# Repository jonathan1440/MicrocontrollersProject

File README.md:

# MicrocontrollersProject
 Hands-free deodorant dispenser

## Parts List
- 3x 1µF capacitors
- 1x 10µF capacitor
- 1x 2x3 header
- 1x 1x3 header
- 1x 1x4 header
- 1x transistor
- 1x Q3 crystal
- 2x 22 Ohm resistors
- 3x 10k Ohm resistors
- 2x buttons
- 1x 3 prong switch
- 1x AT90USB162 chip
- 1x USB micro B port
- 1x servo
- 1x Sharp GP2D02 IR sensor

## User Instructions
Flip the switch to on. Position yourself directly in front of the sensor. To tirgger the servo, move within 8-13 cm of the sensor. To release the servo, don't be within 8-13cm of the sensor.

## Code Overview
Pinout:
- PC7 - "on/off" switch
- PB5 - sensor output
- PB6 - sensor Vin
- PB7 - servo

GetDist() reads the data value from the IR sensor. The biggest roadblock was figguring out that the IR sensor was open drain. Otherwise the function just follows the Sharp GP2302 datasheet.

The main() function configures the pinout and initializes the PWM timer (clear OC0A at match, fast PWM mode, top defaults to 0xFF, prescaler = 64). The while loop waits until the switch is positioned at "on," and then moves the servo to the appropriate position if the user is within range or out of range. If the user is not detected by the sensor, the servo is turned off.

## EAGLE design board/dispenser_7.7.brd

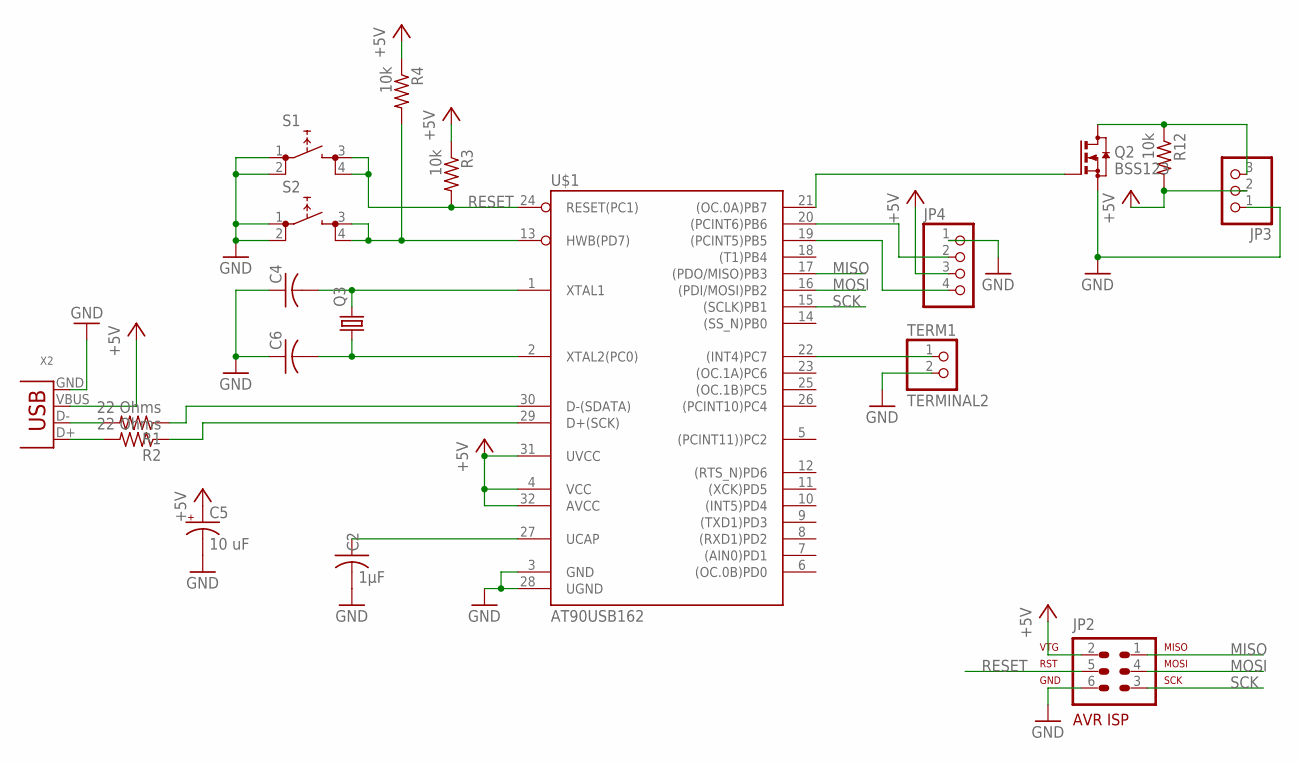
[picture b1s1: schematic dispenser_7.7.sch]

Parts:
C2: 1µF; C050-025X075
C4, C6: C-USC050-025X075; C050-025X075
C5: 10 uF; E2,5-5
JP2: AVR-ISP-6
JP3: PINHD-1X3; 1X03
JP4: PINHD-1X4; 1X04
Q2: BSS123; SOT23
Q3: CRYSTALHC49S; HC49/S
R1, R2: 22 Ohms; 0207/7
R3, R4, R12: 10k; 0207/7
S1, S2: PUSHBUTTON; TL1105SP
TERM1: TERMINAL2; TERM2
U$1: AT90USB162; TQFP32-08
X2: USB-MB-H

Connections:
+5V: C5.+, JP2.2, JP3.2, JP4.3, R3.1, R4.1, R12.2, U$1.4 (VCC), U$1.31 (UVCC), U$1.32 (AVCC), X2.VBUS
GND: C2.2, C4.1, C5.-, C6.1, JP2.6, JP3.1, JP4.1, Q2.2 (S), S1.1 (0), S1.2 (0), S2.1 (0), S2.2 (0), TERM1.2, U$1.3 (GND), U$1.28 (UGND), X2.GND
MISO: JP2.1, U$1.17 ((PDO/MISO)PB3)
MOSI: JP2.4, U$1.16 ((PDI/MOSI)PB2)
unnamed: JP4.4, U$1.19 ((PCINT5)PB5)
unnamed: JP4.2, U$1.20 ((PCINT6)PB6)
unnamed: C4.2, Q3.2, U$1.1 (XTAL1)
unnamed: Q2.1 (G), U$1.21 ((OC.0A)PB7)
unnamed: C6.2, Q3.1, U$1.2 (XTAL2(PC0))
unnamed: R2.1, U$1.29 (D+(SCK))
unnamed: TERM1.1, U$1.22 ((INT4)PC7)
unnamed: R2.2, X2.D+
unnamed: R1.2, X2.D-
unnamed: C2.1, U$1.27 (UCAP)
unnamed: R1.1, U$1.30 (D-(SDATA))
unnamed: R4.2, S2.3 (1), S2.4 (1), U$1.13 (HWB(PD7))
unnamed: JP3.3, Q2.3 (D), R12.1
RESET: JP2.5, R3.2, S1.3 (1), S1.4 (1), U$1.24 (RESET(PC1))
SCK: JP2.3, U$1.15 ((SCLK)PB1)

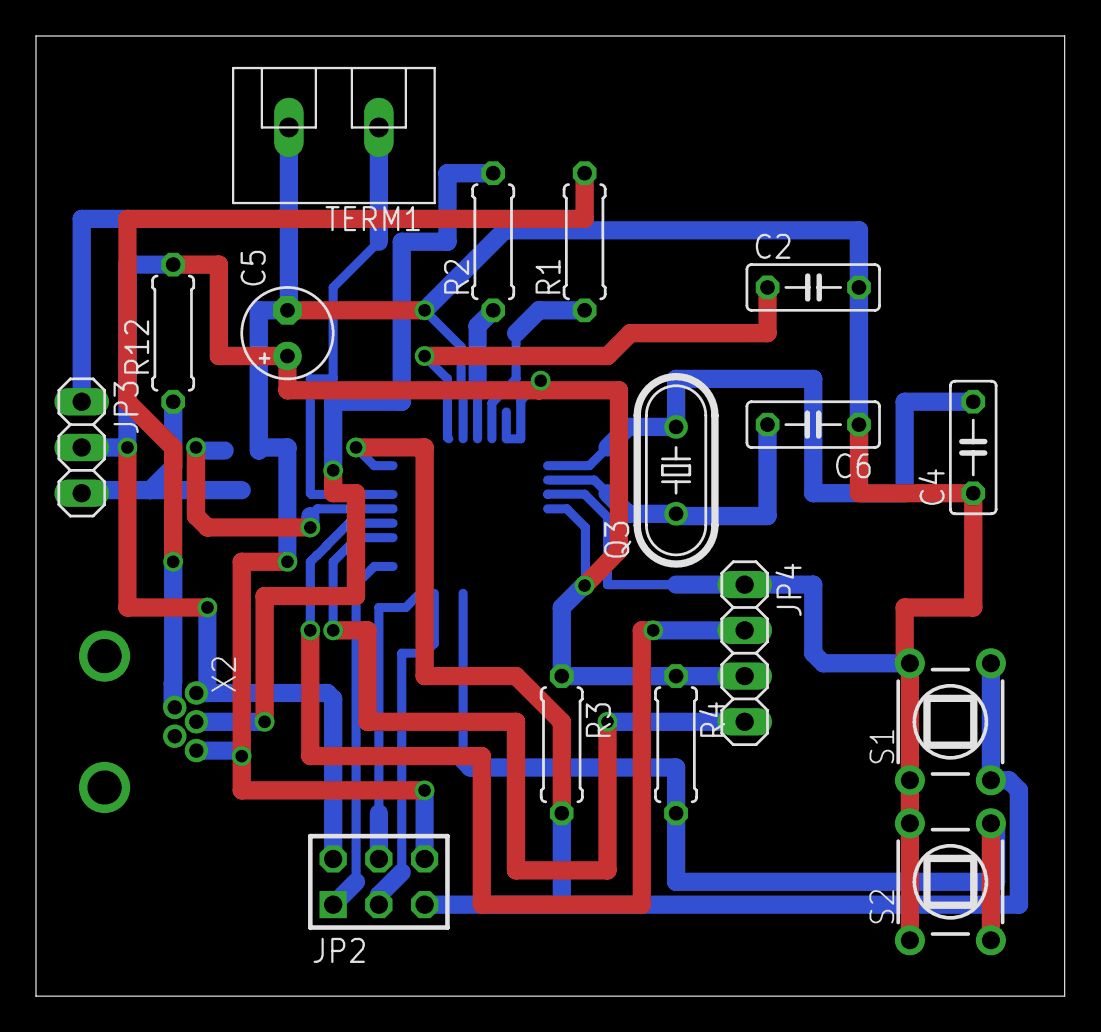
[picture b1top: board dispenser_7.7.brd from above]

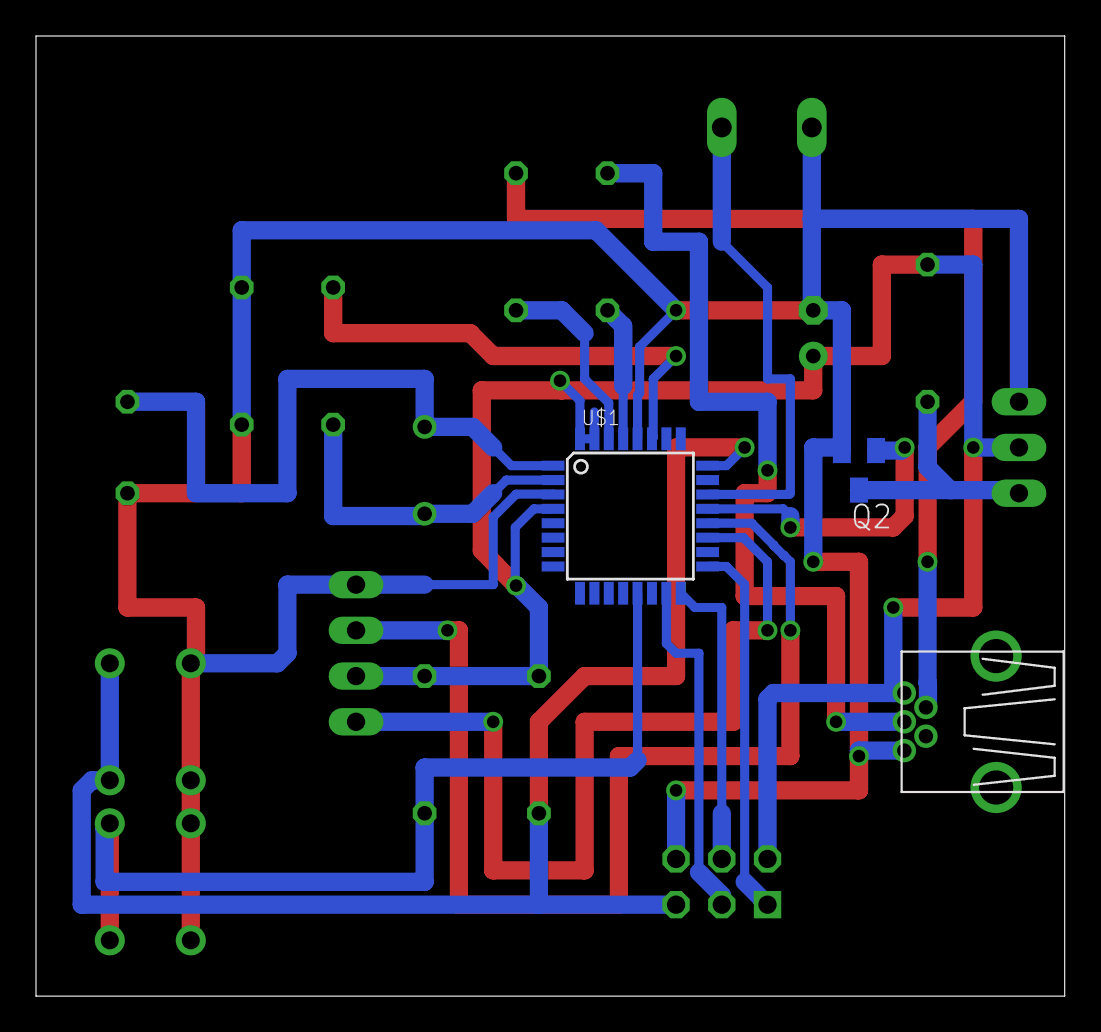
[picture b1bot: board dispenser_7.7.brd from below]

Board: 2 copper layers, 57.1 x 53.3 mm, 19 parts (2 on the bottom side), 19 nets.

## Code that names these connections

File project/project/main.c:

/*
 * project.c
 *
 * Created: 12/14/2020 1:09:56 PM
 * Author : Jonathan Ziesmer
 */ 

#define F_CPU 1000000UL

#define MIN_RANGE 0xD2  // 8 cm or ~13 cm
#define MAX_RANGE 0xF0  // ~10.5 cm
#define OUT_RANGE 0xA6  // 21.5 cm

#include <avr/io.h>
#include <util/delay.h>
#include <stdio.h>
#include <avr/interrupt.h>


uint8_t GetDist(void)
{
	// PB6 - Vin to sensor
	// PB5 - Out of sensor
	
	DDRB |= (1<<DDB6);  // set PB6 low
	_delay_ms(20);
	while(!(PINB & 0x20)){;}  // wait for PB5 to go high
	DDRB &= ~(1<<DDB6);  // set PB6 high
	_delay_us(100);  // wait .1ms
	
	uint8_t counter = 0;
	uint8_t data = 0x00;
	while(counter < 8)
	{
		DDRB |= (1<<DDB6);  // set PB6 low
		_delay_us(100);  // wait .1ms
		uint8_t temp = (PINB & 0x20) >> 5;  // mask with PB5
		data = (data << 1) | temp;
		DDRB &= ~(1<<DDB6);  // set PB6 high
		_delay_us(100);  // wait .1ms
		counter ++;
	}
	
	_delay_ms(2);  // wait 1.5 or more to put sensor in sleep mode
	
	return data;
}


int main(void)
{
	// PC7 - "on/off" switch
	// PB6 - Sensor Vin
	// PB5 - Sensor output
	// PB7 - servo
	
	DDRC = (0<<DDC7);  // set PC7 to input	
	PORTC = (1<<PC7);  // set PC7 to pullup
	
	DDRB = (1<<DDB6) | (1<<DDB7);  // set PB6 & PB7 to output, set PB5 to input
	PORTB = (1<<PB7) | (0<<PB6);  // set PB7 high, PB6 low
	
	
	// timer PWM init
	TCCR0A = (1<<COM0A0) | (1<<COM0A1) | (1<<WGM01) | (1<<WGM00);  // clear OC0A at match, set timer to fast PWM, top defaults to 0xFF
	
	int moved = 1;
	
    while (1) 
    {
		while(!(PINC & 0x80)) {;}  // wait while PC7 not high
		
		uint8_t dist = GetDist();
		if(dist > MIN_RANGE && dist < MAX_RANGE)  // if user within range
		{
			OCR0A = 37;  // set servo position
			TCCR0B = (1<<CS01) | (1<<CS00);  // start timer PWM
			moved = 0;			
		}
		else if(dist < MIN_RANGE && dist > OUT_RANGE)  // if user moving in/out of range
		{
			OCR0A = 20;  // set servo position
			TCCR0B = (1<<CS01) | (1<<CS00);  // start timer PWM
			moved = 0;			
		}
		else{  // if user out of range
			TCCR0B = 0;  // stop timer
		}
		
		if(!moved)
		{
			_delay_ms(450);  // wait for servo to finish motion
			moved = 1;
		}
    }
}

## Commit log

2021-04-14 Final documentation
